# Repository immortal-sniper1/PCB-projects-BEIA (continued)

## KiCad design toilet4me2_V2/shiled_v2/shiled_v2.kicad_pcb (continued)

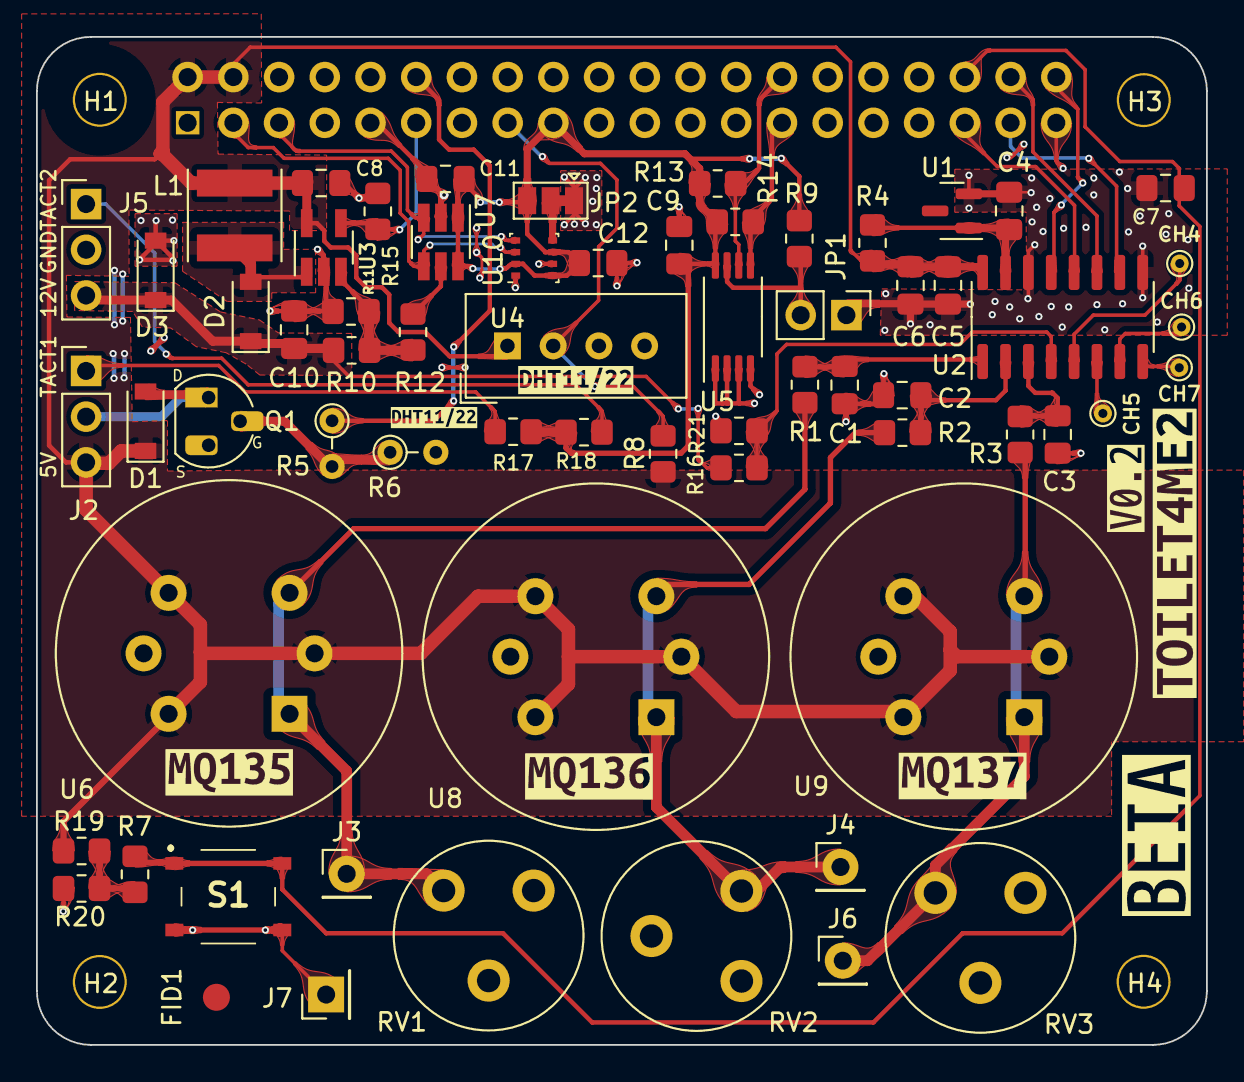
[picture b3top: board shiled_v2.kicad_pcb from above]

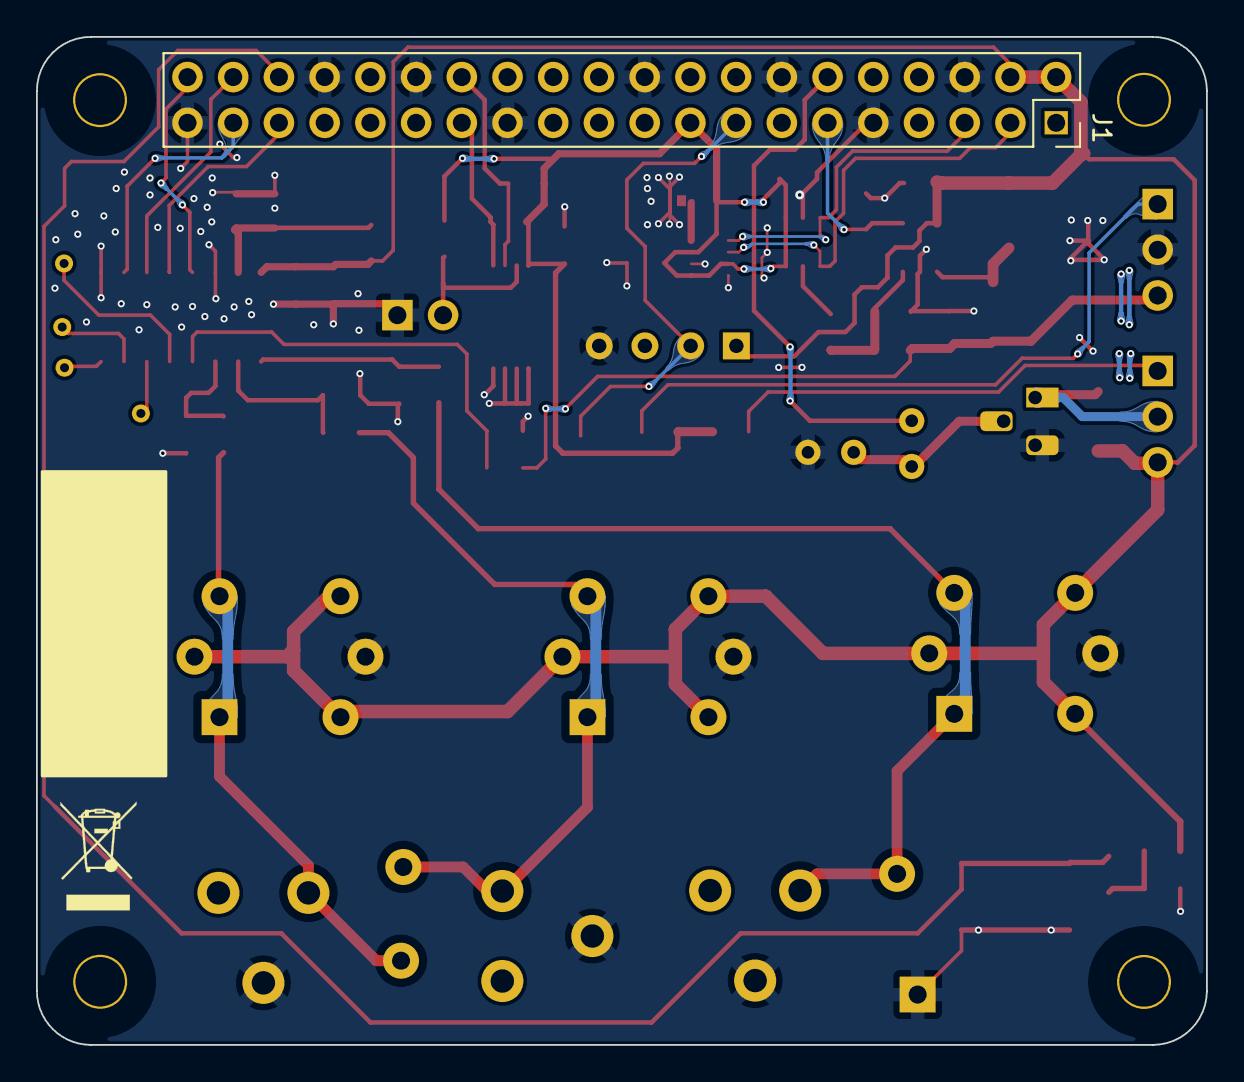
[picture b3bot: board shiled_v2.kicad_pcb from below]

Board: 2 copper layers, 65.0 x 56.0 mm, 79 parts (2 on the bottom side), 38 nets.

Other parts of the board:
kibuzzard-62DA5EB2: G***; kibuzzard-62DA5EB2
kibuzzard-62E79C6C: G***; kibuzzard-62E79C6C
kibuzzard-62E79CA0: G***; kibuzzard-62E79CA0
kibuzzard-62E789B0: G***; kibuzzard-62E789B0
kibuzzard-62E797EE: G***; kibuzzard-62E797EE
kibuzzard-62E797F8: G***; kibuzzard-62E797F8
kibuzzard-62E79804: G***; kibuzzard-62E79804
kibuzzard-62EB9840: G***; kibuzzard-62EB9840

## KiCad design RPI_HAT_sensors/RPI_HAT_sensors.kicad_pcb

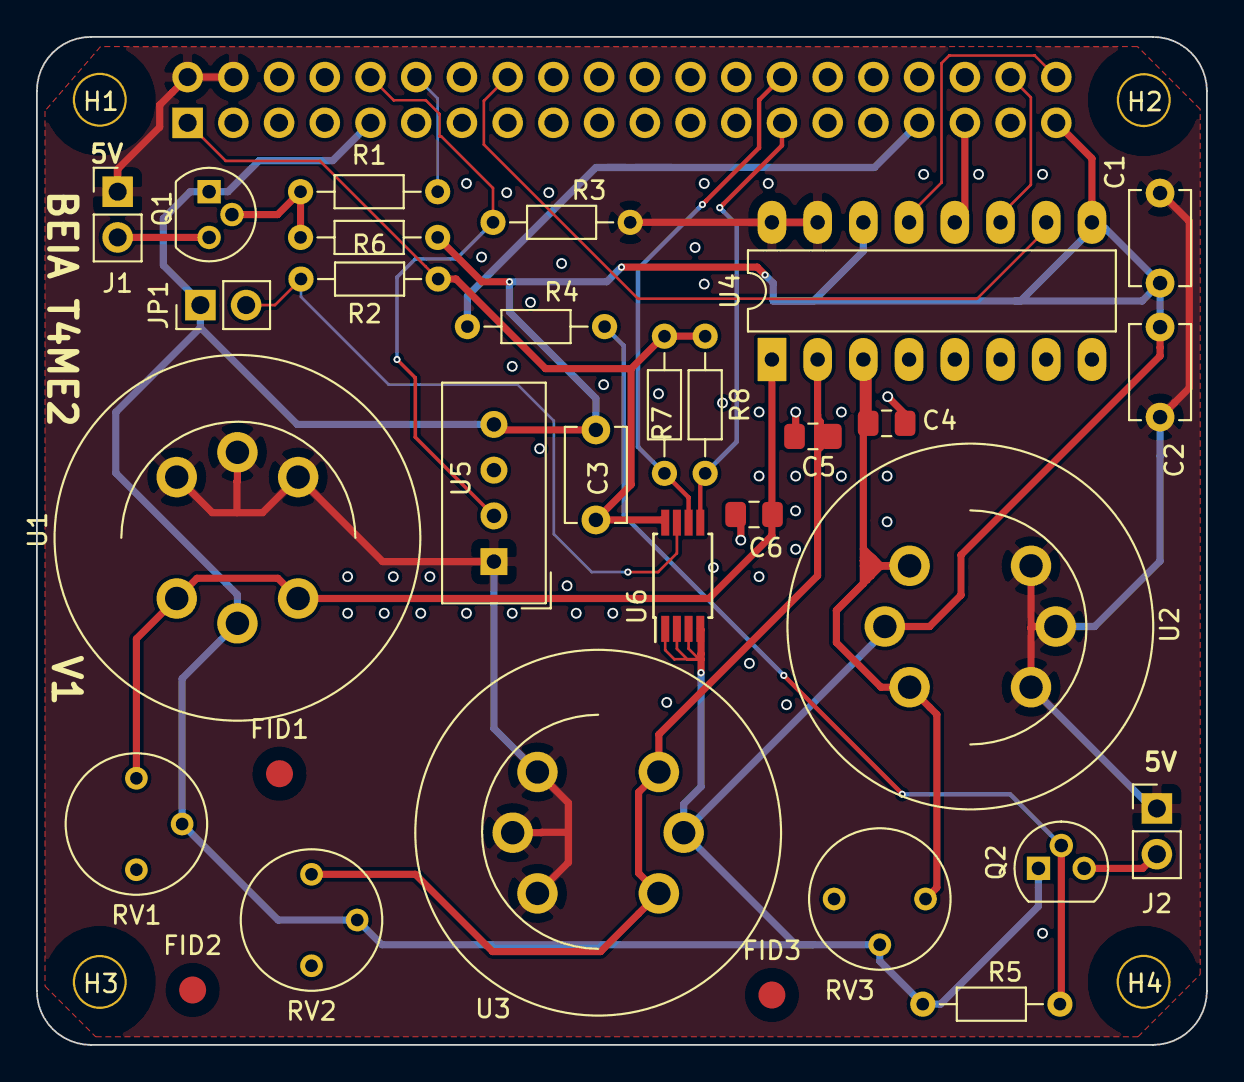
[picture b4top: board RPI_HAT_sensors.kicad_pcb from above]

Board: 2 copper layers, 65.0 x 56.0 mm, 36 parts (1 on the bottom side), 20 nets.

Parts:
C1: 10u; C_Disc_D5.1mm_W3.2mm_P5.00mm
C2, C3: 1u; C_Disc_D5.1mm_W3.2mm_P5.00mm
C4, C5, C6: 1u; C_0805_2012Metric_Pad1.15x1.40mm_HandSolder
FID1, FID2, FID3: Fiducial; Fiducial_1.5mm_Mask3mm
H1, H2, H3, H4: 3mm_Mounting_Hole; NPTH_3mm_ID
J1, J2: MOTOR; PinHeader_1x02_P2.54mm_Vertical
J3: 40HAT; PinSocket_2x20_P2.54mm_Vertical
JP1: Jumper_2_Open; PinHeader_1x02_P2.54mm_Vertical
Q1, Q2: Q_NMOS_SGD; TO-92
R1, R4: 220+; R_Axial_DIN0204_L3.6mm_D1.6mm_P7.62mm_Horizontal
R2, R5: 10k; R_Axial_DIN0204_L3.6mm_D1.6mm_P7.62mm_Horizontal
R3: 5.1k; R_Axial_DIN0204_L3.6mm_D1.6mm_P7.62mm_Horizontal
R6, R7, R8: 3K9; R_Axial_DIN0204_L3.6mm_D1.6mm_P7.62mm_Horizontal
RV1, RV2, RV3: R_POT; Potentiometer_Bourns_3339P_Vertical
U1: MQ135
U2: MQ137; MQ135
U3: MQ136; MQ135
U4: MCP3208; DIP-16_W7.62mm_LongPads
U5: DHT11; Aosong_DHT11_5.5x12.0_P2.54mm
U6: CAT24C32-raspberrypi_hat; TSSOP-8_4.4x3mm_P0.65mm

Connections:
+3V3: C3.2, J3.1, R6.2, R7.1, R8.1, U6.8
+5V: C1.1, C2.1, J1.1, J2.1, J3.2, J3.4, R3.1, U1.1, U1.2, U1.3, U2.1, U2.2, U2.3, U3.1, U3.2, U3.3, U4.15, U4.16, U5.1
/ADC1: C6.2, RV1.1, U1.4, U1.6, U4.1
/ADC2: C5.2, RV2.1, U3.4, U3.6, U4.2
/ADC3: C4.2, RV3.1, U2.4, U2.6, U4.3
/CLK: J3.40, U4.13
/DHT11: J3.10, R3.2, U5.2
/DIN: J3.38, U4.11
/DOUT: J3.35, U4.12
/EEPROM_SC: J3.28, R7.2, U6.6
/EEPROM_SD: J3.27, R8.2, U6.5
/ENABLE: J3.16, U4.10
/motor_control: J3.12, R1.1
/motor_control2: J3.33, R4.1
GND: C1.2, C2.2, C3.1, C4.1, C5.1, C6.1, J3.6, J3.9, J3.14, J3.20, J3.25, J3.30, J3.34, J3.39, JP1.1, Q1.1, Q2.1, R2.2, R5.2, RV1.2, RV2.2, RV3.2, U1.5, U2.5, U3.5, U4.9, U4.14, U5.4, U6.1, U6.2, U6.3, U6.4
unnamed: J1.2, Q1.3
unnamed: J2.2, Q2.3
unnamed: JP1.2, R6.1, U6.7
unnamed: Q1.2, R1.2, R2.1
unnamed: Q2.2, R4.2, R5.1

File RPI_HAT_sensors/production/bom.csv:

Designator,Footprint,Quantity,Value,LCSC Part #
H1,NPTH_3mm_ID,1,3mm_Mounting_Hole,
H2,NPTH_3mm_ID,1,3mm_Mounting_Hole,
H3,NPTH_3mm_ID,1,3mm_Mounting_Hole,
H4,NPTH_3mm_ID,1,3mm_Mounting_Hole,
RV1,Potentiometer_Bourns_3339P_Vertical,1,R_POT,
RV2,Potentiometer_Bourns_3339P_Vertical,1,R_POT,
RV3,Potentiometer_Bourns_3339P_Vertical,1,R_POT,
U2,MQ135,1,MQ137,
U3,MQ135,1,MQ136,
J1,PinHeader_1x02_P2.54mm_Vertical,1,MOTOR,
Q1,TO-92,1,Q_NMOS_SGD,
R1,R_Axial_DIN0204_L3.6mm_D1.6mm_P7.62mm_Horizontal,1,220+,
R2,R_Axial_DIN0204_L3.6mm_D1.6mm_P7.62mm_Horizontal,1,10k,
R3,R_Axial_DIN0204_L3.6mm_D1.6mm_P7.62mm_Horizontal,1,5.1k,
U5,Aosong_DHT11_5.5x12.0_P2.54mm,1,DHT11,
U4,DIP-16_W7.62mm_LongPads,1,MCP3208,
C1,C_Disc_D5.1mm_W3.2mm_P5.00mm,1,10u,
C2,C_Disc_D5.1mm_W3.2mm_P5.00mm,1,1u,
J2,PinHeader_1x02_P2.54mm_Vertical,1,MOTOR,
R4,R_Axial_DIN0204_L3.6mm_D1.6mm_P7.62mm_Horizontal,1,220+,
R5,R_Axial_DIN0204_L3.6mm_D1.6mm_P7.62mm_Horizontal,1,10k,
Q2,TO-92,1,Q_NMOS_SGD,
FID1,Fiducial_1.5mm_Mask3mm,1,Fiducial,
FID2,Fiducial_1.5mm_Mask3mm,1,Fiducial,
FID3,Fiducial_1.5mm_Mask3mm,1,Fiducial,
C3,C_Disc_D5.1mm_W3.2mm_P5.00mm,1,1u,
JP1,PinHeader_1x02_P2.54mm_Vertical,1,Jumper_2_Open,
R6,R_Axial_DIN0204_L3.6mm_D1.6mm_P7.62mm_Horizontal,1,3K9,
R8,R_Axial_DIN0204_L3.6mm_D1.6mm_P7.62mm_Horizontal,1,3K9,
U6,TSSOP-8_4.4x3mm_P0.65mm,1,CAT24C32-raspberrypi_hat,
R7,R_Axial_DIN0204_L3.6mm_D1.6mm_P7.62mm_Horizontal,1,3K9,
U1,MQ135,1,MQ135,
C4,C_0805_2012Metric_Pad1.15x1.40mm_HandSolder,1,1u,
C5,C_0805_2012Metric_Pad1.15x1.40mm_HandSolder,1,1u,
C6,C_0805_2012Metric_Pad1.15x1.40mm_HandSolder,1,1u,
J3,PinSocket_2x20_P2.54mm_Vertical,1,40HAT,

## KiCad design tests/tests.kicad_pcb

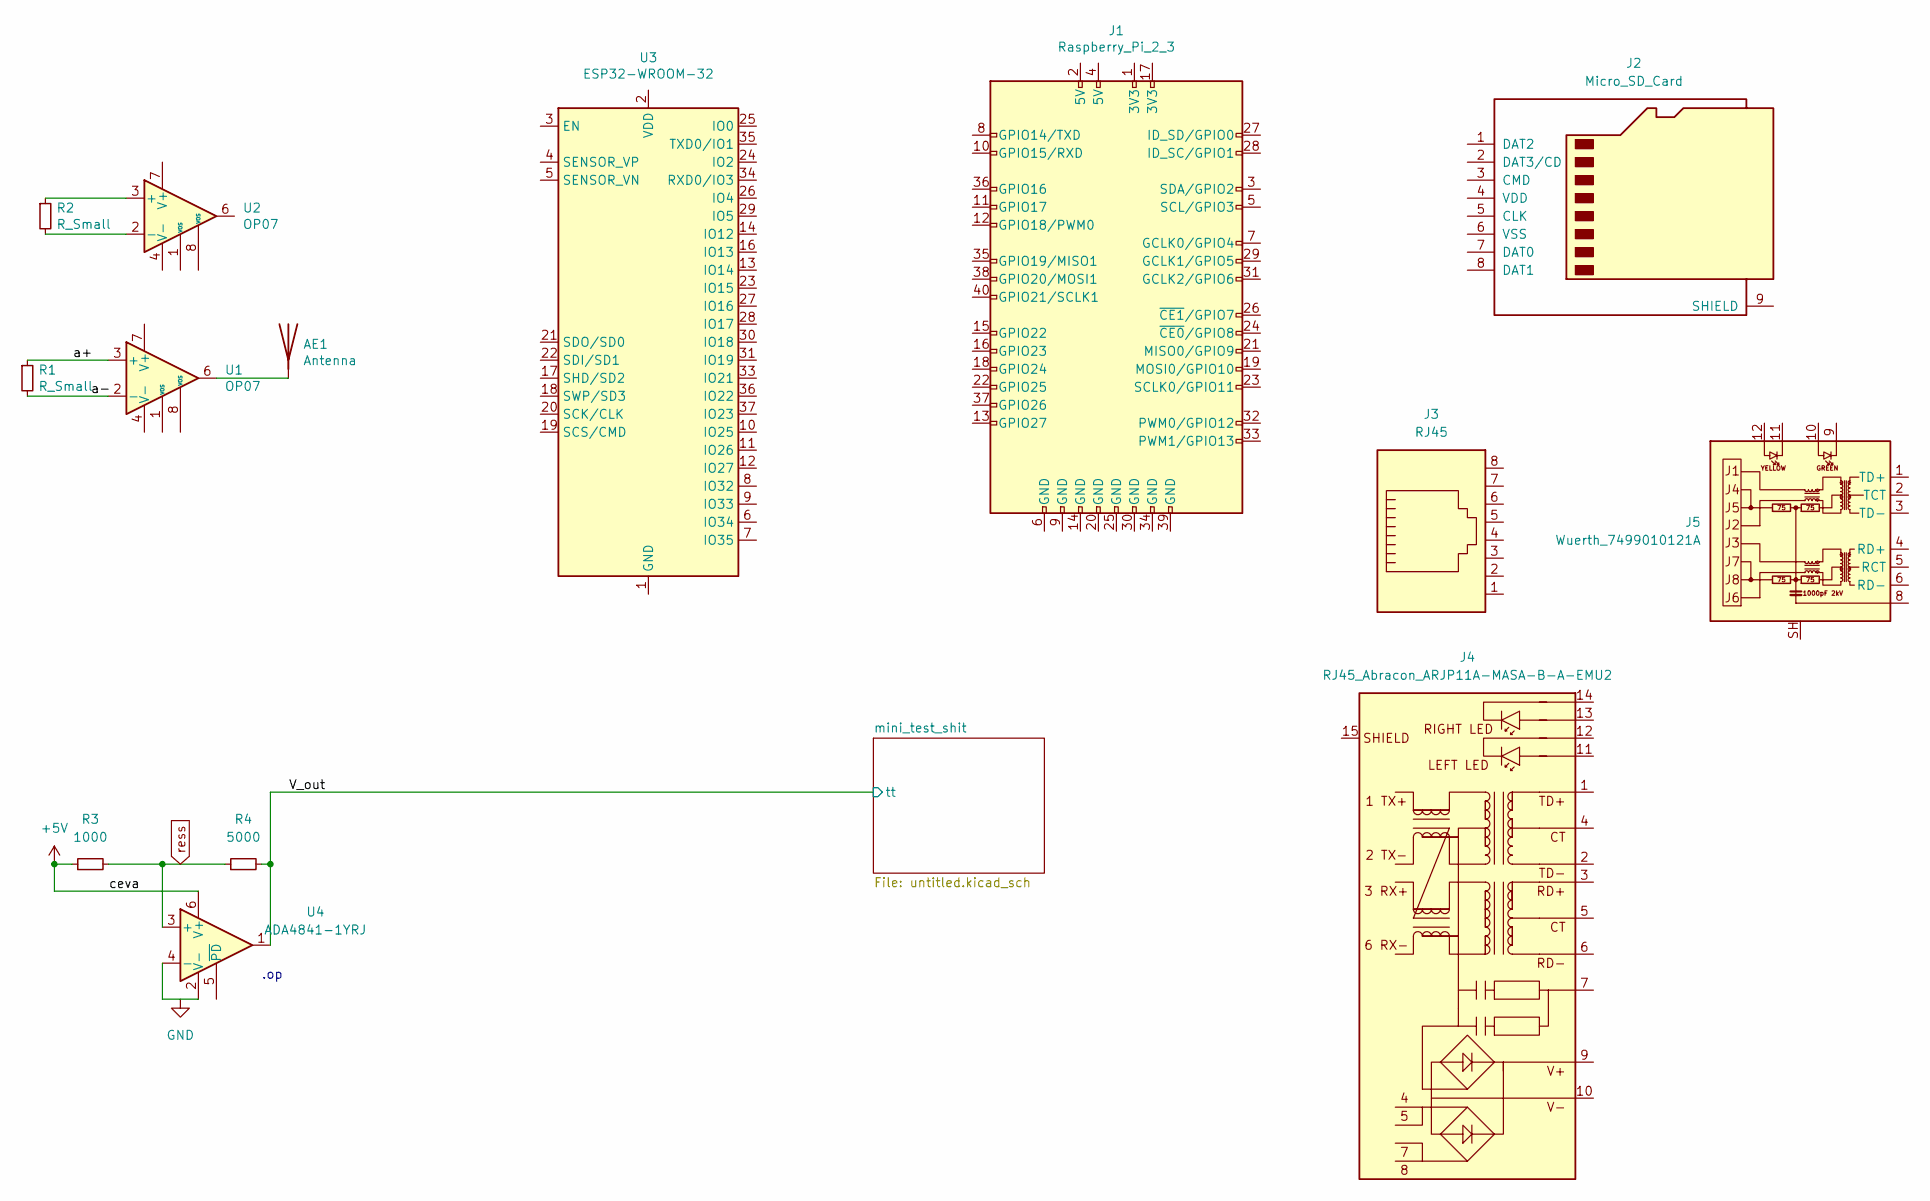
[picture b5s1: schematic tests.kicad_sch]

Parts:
AE1: Antenna; Texas_SWRA117D_2.4GHz_Left
J1: Raspberry_Pi_2_3
J2: Micro_SD_Card; microSD_HC_Hirose_DM3D-SF
J3: RJ45; RJ45_Amphenol_RJHSE538X
J4: RJ45_Abracon_ARJP11A-MASA-B-A-EMU2; RJ45_Abracon_ARJP11A-MA_Horizontal
J5: Wuerth_7499010121A; RJ45_Wuerth_7499010121A_Horizontal
R1, R2: R_Small; R_0805_2012Metric_Pad1.15x1.40mm_HandSolder
R3: 1000; R_Axial_DIN0204_L3.6mm_D1.6mm_P7.62mm_Horizontal
R4: 5000; R_Axial_DIN0204_L3.6mm_D1.6mm_P7.62mm_Horizontal
U1, U2: OP07; DIP-8_W7.62mm_LongPads
U3: ESP32-WROOM-32
U4: ADA4841-1YRJ; SOT-23-6

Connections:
+5V: R3.1, U4.6 (V+)
/V_out: R4.2, U4.1; also elsewhere on the board
/a+: R1.1, U1.3 (+)
/a-: R1.2, U1.2 (-)
unnamed: AE1.1 (A), U1.6
unnamed: R2.1, U2.3 (+)
unnamed: R2.2, U2.2 (-)
unnamed: U3.1 (GND), U3.15 (GND), U3.38 (GND), U3.39 (GND)
unnamed: U4.2 (V-), U4.4 (-)
ress: R3.2, R4.1, U4.3 (+)

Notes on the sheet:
.op

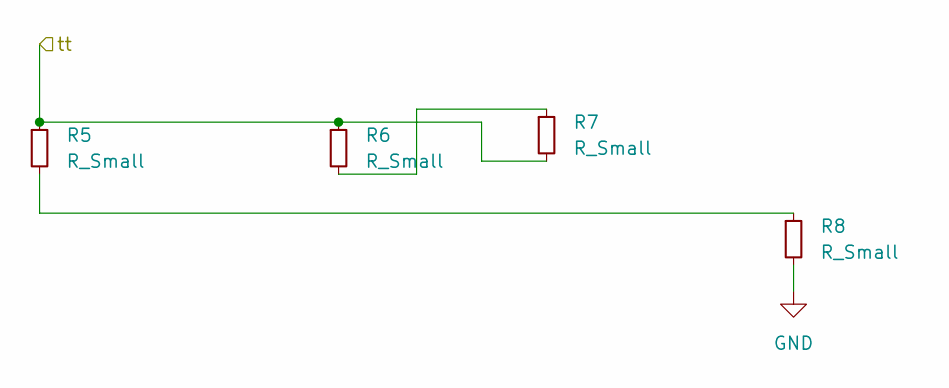
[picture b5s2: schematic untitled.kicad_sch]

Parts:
R5, R6, R7, R8: R_Small; R_Axial_DIN0204_L3.6mm_D1.6mm_P7.62mm_Horizontal

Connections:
/V_out: R5.1, R6.1, R7.2; also elsewhere on the board
GND: R8.2
unnamed: R5.2, R8.1
unnamed: R6.2, R7.1

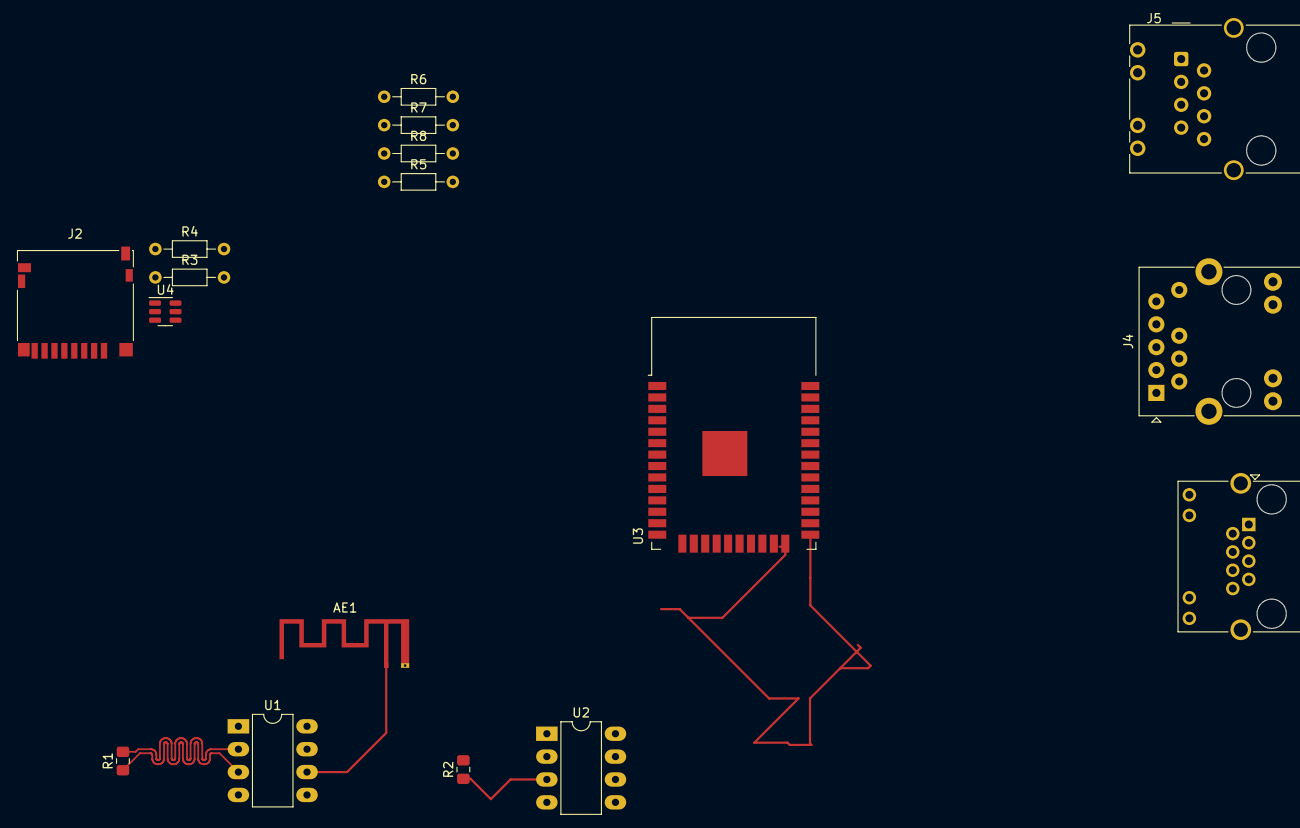
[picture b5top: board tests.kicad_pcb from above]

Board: 2 copper layers, 17 parts (0 on the bottom side), 12 nets.

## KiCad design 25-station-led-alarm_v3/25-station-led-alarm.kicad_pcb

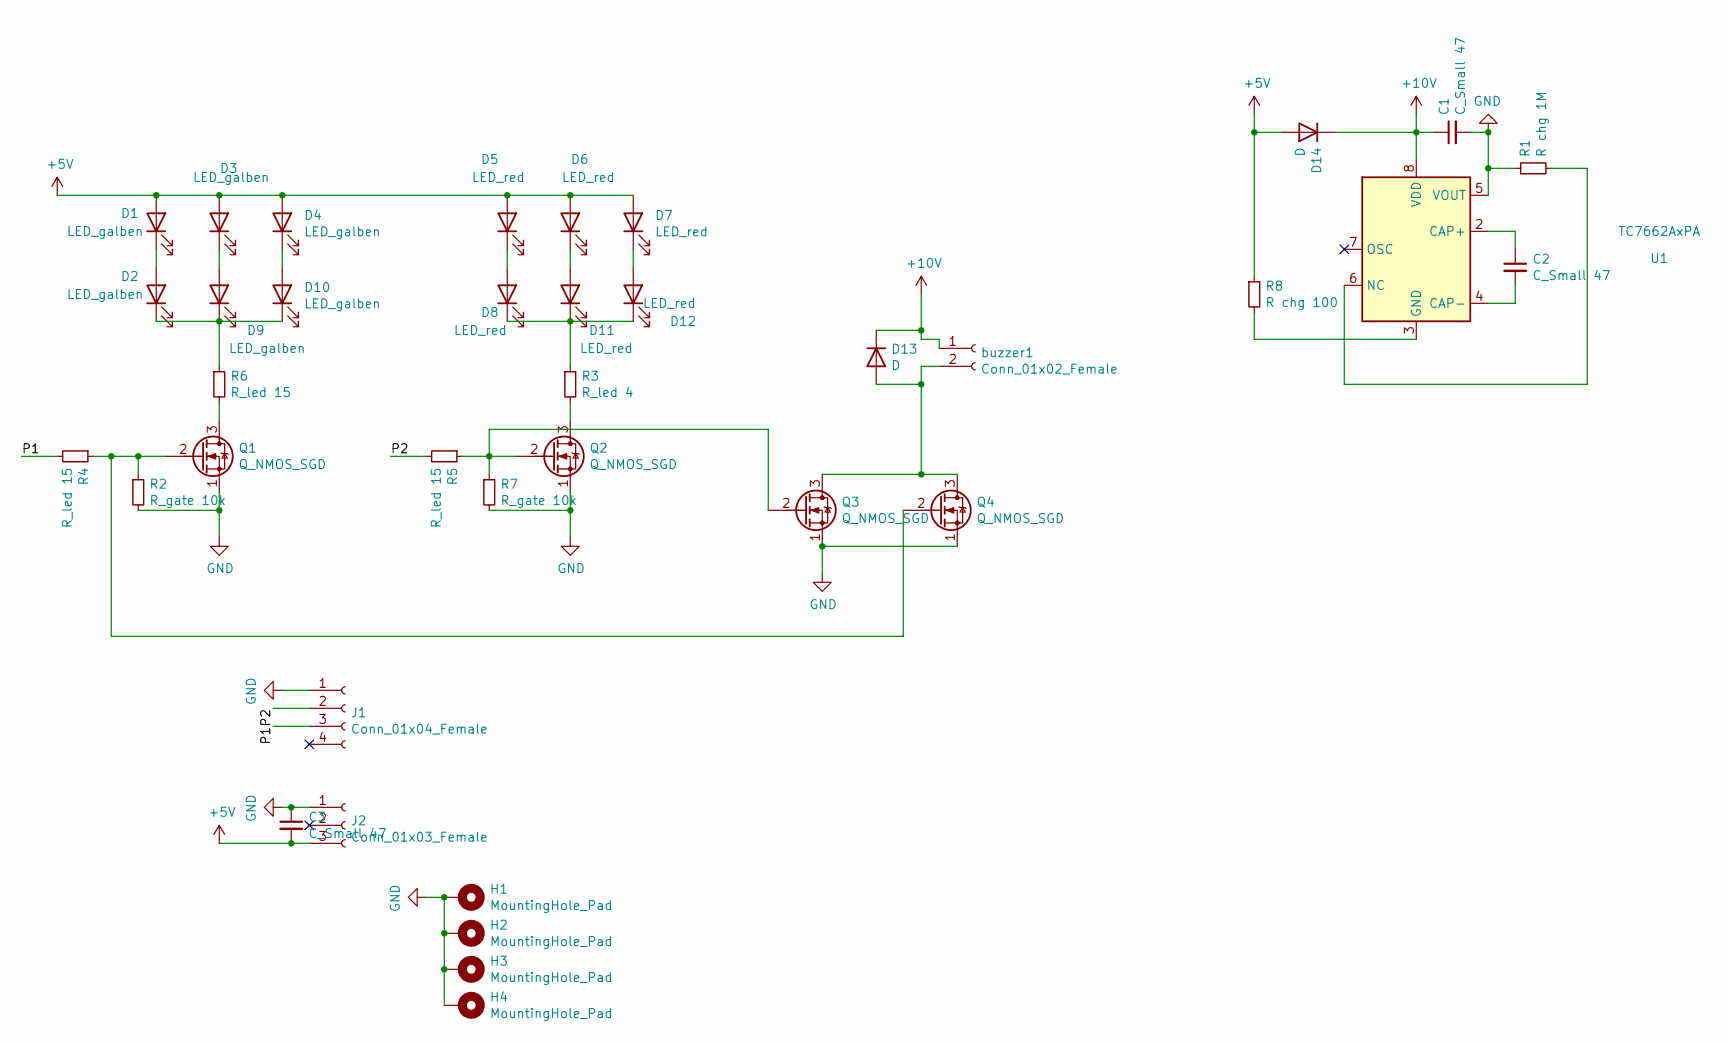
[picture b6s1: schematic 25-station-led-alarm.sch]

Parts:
C1, C2: C_Small 47; C_Disc_D8.0mm_W5.0mm_P5.00mm
C3: C_Small 47; C_Rect_L9.0mm_W3.2mm_P7.50mm_MKT
D1, D2, D3, D4, D9, D10: LED_galben; LED_D3.0mm
D5, D6, D7, D8, D11, D12: LED_red; LED_D5.0mm
D13, D14: D; D_DO-15_P12.70mm_Horizontal
H1, H2, H3, H4: MountingHole_Pad; MountingHole_4.3mm_M4
J1: Conn_01x04_Female; PinHeader_1x04_P2.54mm_Vertical
J2: Conn_01x03_Female; PinHeader_1x03_P2.54mm_Vertical
Q1, Q2, Q3, Q4: Q_NMOS_SGD; TO-92
R1: R chg 1M; R_Axial_DIN0204_L3.6mm_D1.6mm_P7.62mm_Horizontal
R2, R7: R_gate 10k; R_Axial_DIN0309_L9.0mm_D3.2mm_P15.24mm_Horizontal
R3: R_led 4; R_Axial_DIN0309_L9.0mm_D3.2mm_P12.70mm_Horizontal
R4, R5, R6: R_led 15; R_Axial_DIN0309_L9.0mm_D3.2mm_P12.70mm_Horizontal
R8: R chg 100; R_Axial_DIN0414_L11.9mm_D4.5mm_P20.32mm_Horizontal
U1: TC7662AxPA; DIP-8_W7.62mm
buzzer1: Conn_01x02_Female; PinHeader_1x02_P2.54mm_Vertical

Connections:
+5V: C3.2, D1.2 (A), D3.2 (A), D4.2 (A), D5.2 (A), D6.2 (A), D7.2 (A), D14.2 (A), J2.3, R8.1
+10V: C1.1, D13.1 (K), D14.1 (K), U1.8 (VDD), buzzer1.1
/P1: J1.3, R4.2
/P2: J1.2, R5.2
GND: C1.2, C3.1, H1.1, H2.1, H3.1, H4.1, J1.1, J2.1, Q1.1 (S), Q2.1 (S), Q3.1 (S), Q4.1 (S), R1.1, R2.2, R7.2, U1.5 (VOUT)
unnamed: C2.1, U1.2 (CAP+)
unnamed: C2.2, U1.4 (CAP-)
unnamed: D1.1 (K), D2.2 (A)
unnamed: D3.1 (K), D9.2 (A)
unnamed: D5.1 (K), D8.2 (A)
unnamed: D2.1 (K), D9.1 (K), D10.1 (K), R6.1
unnamed: D4.1 (K), D10.2 (A)
unnamed: D8.1 (K), D11.1 (K), D12.1 (K), R3.1
unnamed: D6.1 (K), D11.2 (A)
unnamed: D7.1 (K), D12.2 (A)
unnamed: D13.2 (A), Q3.3 (D), Q4.3 (D), buzzer1.2
unnamed: Q1.2 (G), Q4.2 (G), R2.1, R4.1
unnamed: Q1.3 (D), R6.2
unnamed: Q2.2 (G), Q3.2 (G), R5.1, R7.1
unnamed: Q2.3 (D), R3.2
unnamed: R1.2, U1.6 (NC)
unnamed: R8.2, U1.3 (GND)

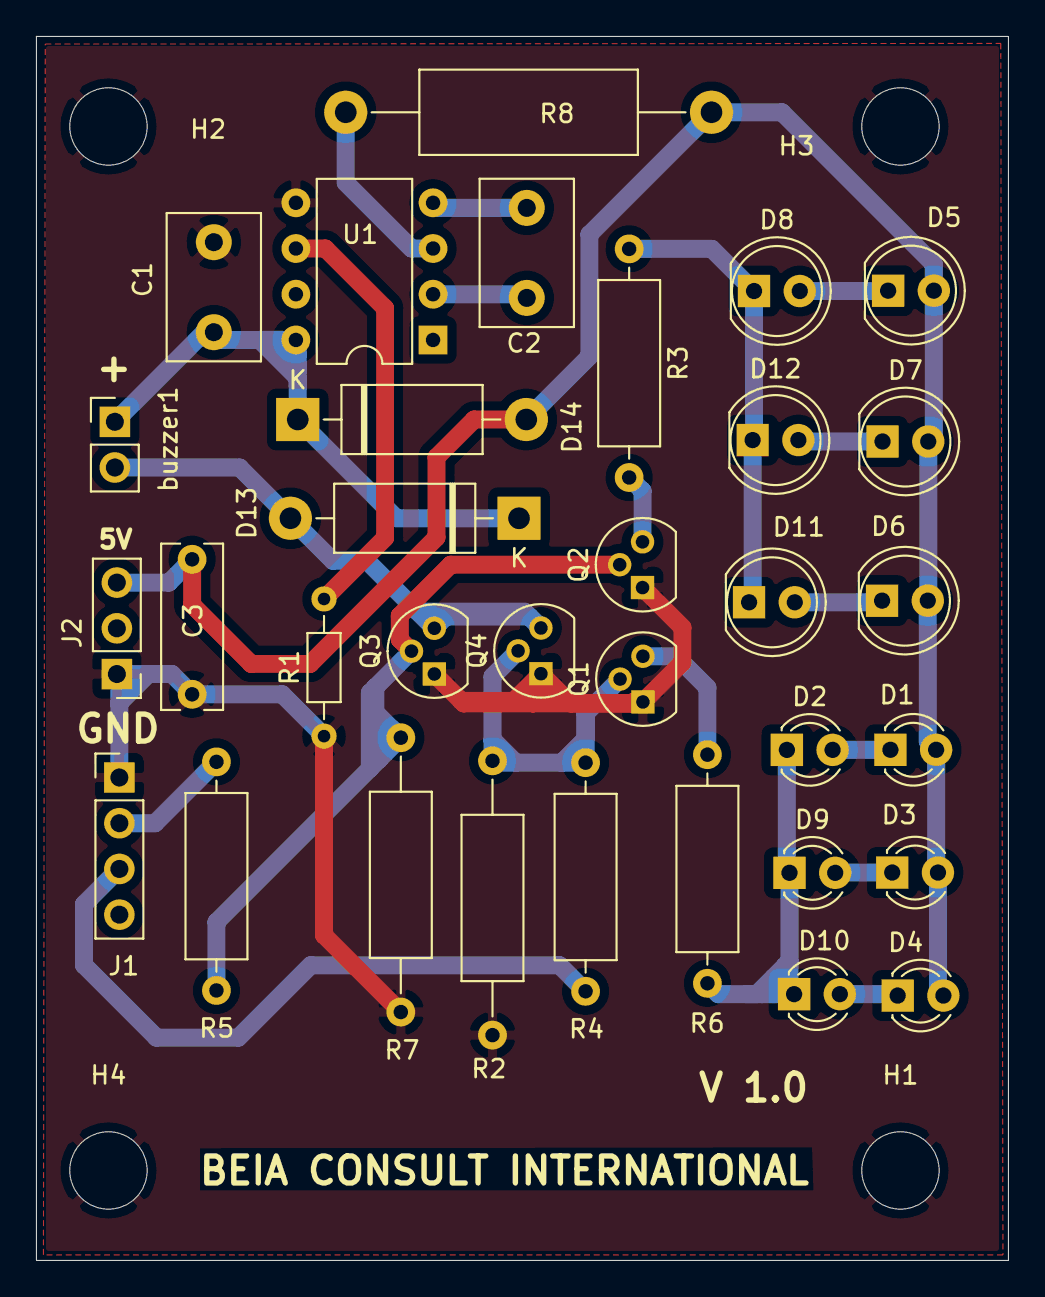
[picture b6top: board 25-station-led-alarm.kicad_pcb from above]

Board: 2 copper layers, 54.0 x 68.0 mm, 37 parts (0 on the bottom side), 22 nets.

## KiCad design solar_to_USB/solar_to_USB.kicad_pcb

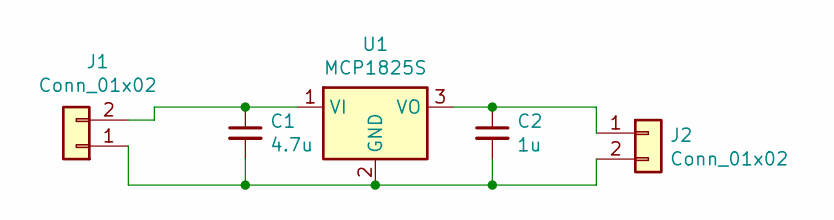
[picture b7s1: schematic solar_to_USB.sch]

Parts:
C1: 4.7u; CP_Radial_D5.0mm_P2.50mm
C2: 1u; CP_Radial_D5.0mm_P2.50mm
J1, J2: Conn_01x02; SolderWire-1.5sqmm_1x02_P6mm_D1.7mm_OD3mm
U1: MCP1825S; TO-220-3_Vertical

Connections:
unnamed: C1.1, J1.2, U1.1 (VI)
unnamed: C1.2, C2.2, J1.1, J2.2, U1.2 (GND)
unnamed: C2.1, J2.1, U1.3 (VO)

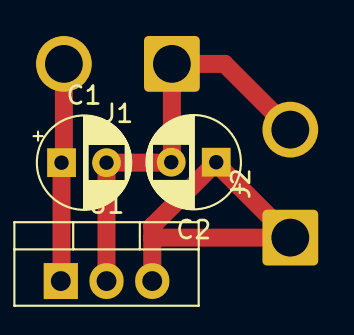
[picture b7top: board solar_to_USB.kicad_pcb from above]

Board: 2 copper layers, 5 parts (0 on the bottom side), 3 nets.

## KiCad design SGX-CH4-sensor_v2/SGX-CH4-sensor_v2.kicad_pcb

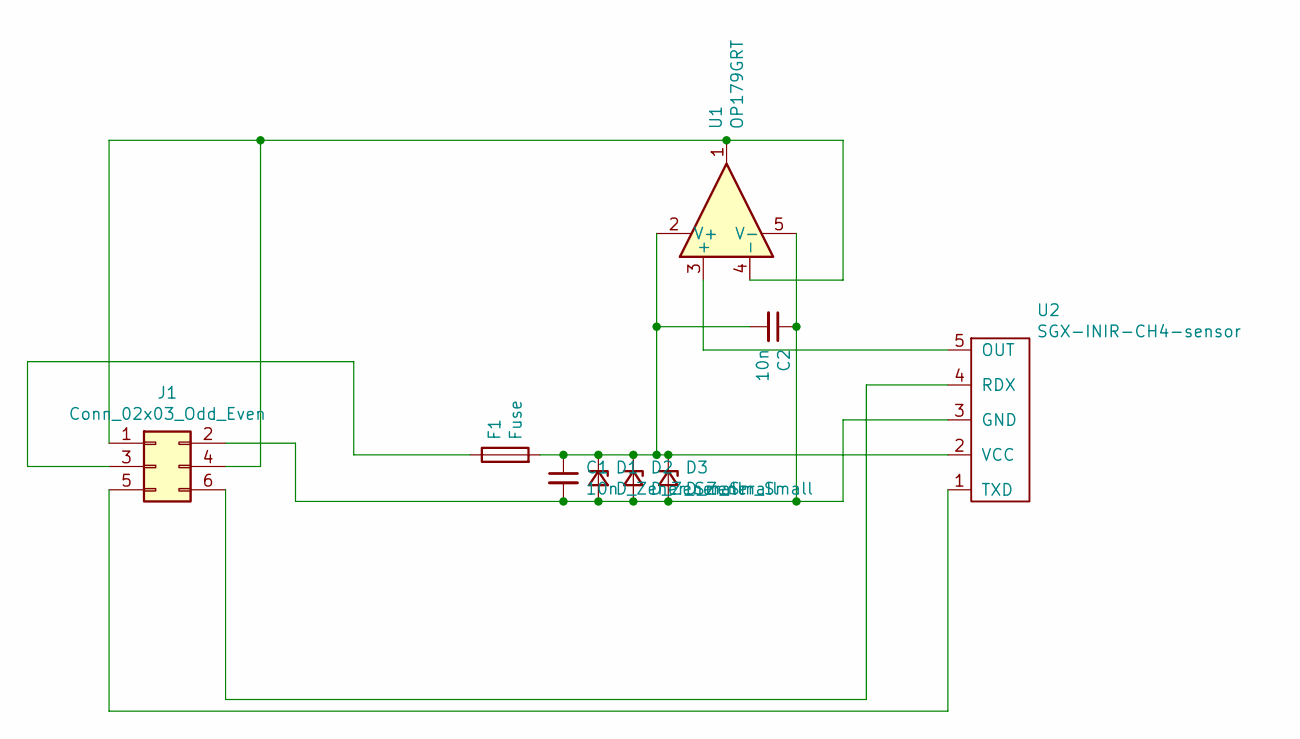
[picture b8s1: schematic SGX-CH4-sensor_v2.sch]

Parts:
C1, C2: 10n; C_Disc_D7.0mm_W2.5mm_P5.00mm
D1, D2, D3: D_Zener_Small; D_DO-35_SOD27_P7.62mm_Horizontal
F1: Fuse; Fuse_BelFuse_0ZRE0012FF_L8.3mm_W3.8mm
J1: Conn_02x03_Odd_Even; PinHeader_2x03_P2.54mm_Vertical
U1: OP179GRT; SOT-23-5
U2: SGX-INIR-CH4-sensor; ch4_sgx

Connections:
unnamed: C1.1, C2.2, D1.1 (K), D2.1 (K), D3.1 (K), F1.2, U1.2 (V+), U2.2 (VCC)
unnamed: C1.2, C2.1, D1.2 (A), D2.2 (A), D3.2 (A), J1.2, U1.5 (V-), U2.3 (GND)
unnamed: F1.1, J1.3
unnamed: J1.1, J1.4, U1.1, U1.4 (-)
unnamed: J1.5, U2.1 (TXD)
unnamed: J1.6, U2.4 (RDX)
unnamed: U1.3 (+), U2.5 (OUT)

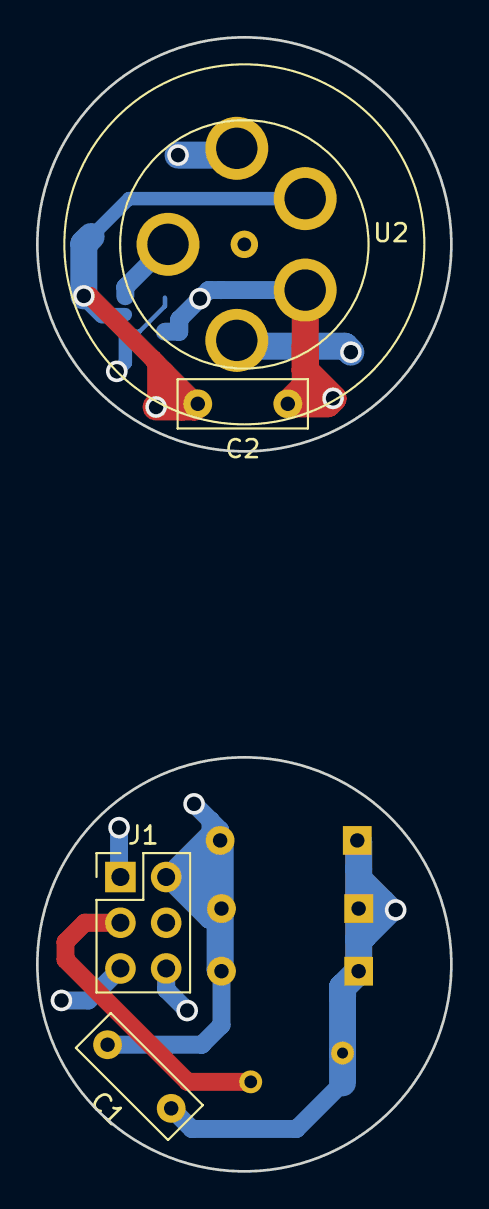
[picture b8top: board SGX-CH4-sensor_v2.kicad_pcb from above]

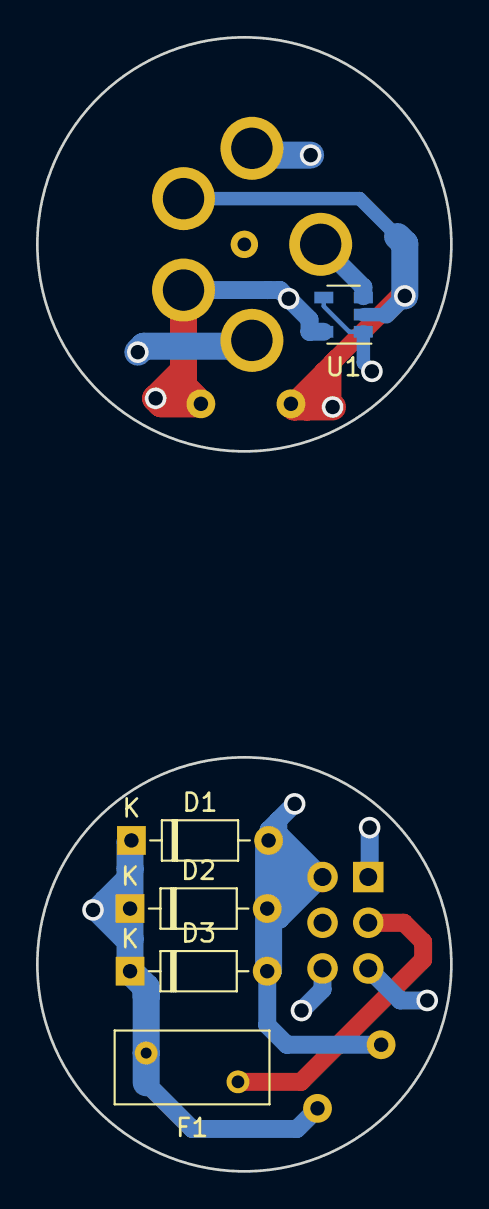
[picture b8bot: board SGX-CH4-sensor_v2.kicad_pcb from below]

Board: 2 copper layers, 23.0 x 63.0 mm, 9 parts (5 on the bottom side), 7 nets.

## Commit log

2021-05-24 fefe
2021-05-25 fewf
2021-05-26 hthet
2021-06-03 fewfew
2021-09-03 rgrg
2021-11-22 finale
2021-12-23 prod files
2022-08-18 Update fp-info-cache
